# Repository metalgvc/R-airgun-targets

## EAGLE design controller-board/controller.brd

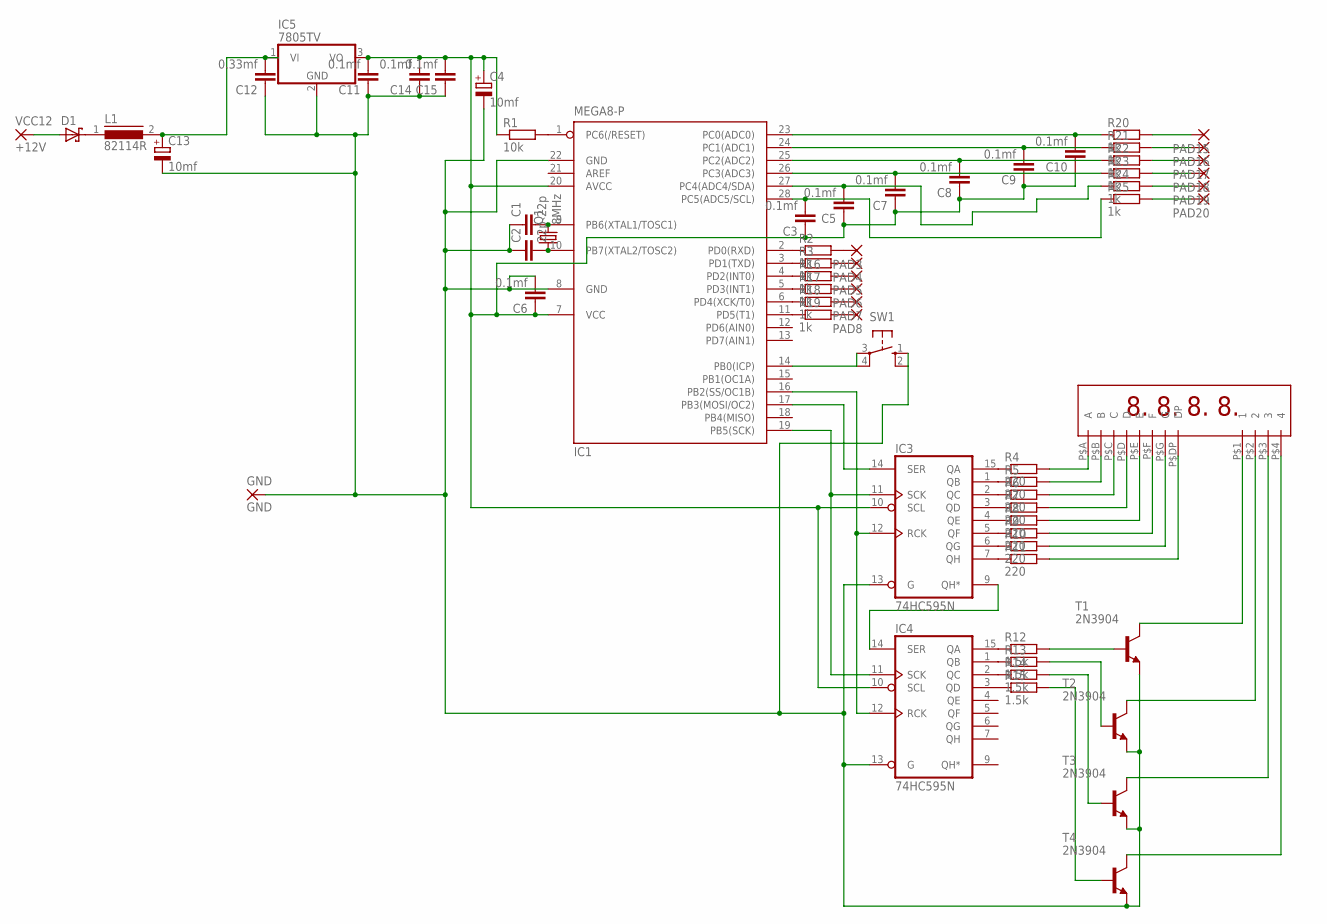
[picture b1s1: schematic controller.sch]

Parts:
C1, C2: 22p; C050-024X044
C3, C5, C6, C7, C8, C9, C10, C11, C14, C15: 0.1mf; C050-024X044
C4, C13: 10mf; E1,8-4
C12: 0.33mf; C050-024X044
D1: SCHOTTKY-DIODEDO35-7; DO35-7
GND: GND; 2,54/1,1
IC1: MEGA8-P; DIL28-3
IC3, IC4: 74HC595N; DIL16
IC5: 7805TV; TO220V
L1: 82114R
PAD3, PAD4, PAD5, PAD6, PAD7, PAD8, PAD15, PAD16, PAD17, PAD18, PAD19, PAD20: 1,6/0,8
Q1: 8MHz; HC49/S
R1: 10k; 0204/7
R2, R3, R16, R17, R18, R19, R20, R21, R22, R23, R24, R25: 1k; 0204/7
R4, R5, R6, R7, R8, R9, R10, R11: 220; 0204/7
R12, R13, R14, R15: 1.5k; 0204/7
SW1: 10-XX; B3F-10XX
T1, T2, T3, T4: 2N3904; TO92
U$1: KL-5641-ASR
VCC12: +12V; 2,54/1,1

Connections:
GND: C1.1, C2.1, C4.-, C6.2, C11.1, C12.1, C13.-, C14.1, C15.1, GND.1, IC1.8 (GND), IC1.22 (GND), IC3.8 (GND), IC3.13 (G), IC4.8 (GND), IC4.13 (G), IC5.2 (GND), SW1.1 (S), SW1.2 (S1), T1.3 (E), T2.3 (E), T3.3 (E), T4.3 (E)
unnamed: IC1.1 (PC6(/RESET)), R1.2
unnamed: D1.C, L1.1
unnamed: IC1.2 (PD0(RXD)), R2.1
unnamed: R4.2, U$1.P$A (A)
unnamed: R5.2, U$1.P$B (B)
unnamed: IC1.3 (PD1(TXD)), R3.1
unnamed: C1.2, IC1.9 (PB6(XTAL1/TOSC1)), Q1.2
unnamed: C2.2, IC1.10 (PB7(XTAL2/TOSC2)), Q1.1
unnamed: R6.2, U$1.P$C (C)
unnamed: R7.2, U$1.P$D (D)
unnamed: R8.2, U$1.P$E (E)
unnamed: R9.2, U$1.P$F (F)
unnamed: IC1.16 (PB2(SS/OC1B)), IC3.12 (RCK), IC4.12 (RCK)
unnamed: IC1.17 (PB3(MOSI/OC2)), IC3.14 (SER)
unnamed: IC1.19 (PB5(SCK)), IC3.11 (SCK), IC4.11 (SCK)
unnamed: C12.2, C13.+, IC5.1 (VI), L1.2
unnamed: R10.2, U$1.P$G (G)
unnamed: R11.2, U$1.P$DP (DP)
unnamed: IC3.15 (QA), R4.1
unnamed: IC3.1 (QB), R5.1
unnamed: IC3.2 (QC), R6.1
unnamed: IC3.3 (QD), R7.1
unnamed: IC3.4 (QE), R8.1
unnamed: IC3.5 (QF), R9.1
unnamed: IC3.6 (QG), R10.1
unnamed: IC3.7 (QH), R11.1
unnamed: IC4.15 (QA), R12.1
unnamed: IC4.1 (QB), R13.1
unnamed: IC4.2 (QC), R14.1
unnamed: IC4.3 (QD), R15.1
unnamed: R12.2, T1.2 (B)
unnamed: R13.2, T2.2 (B)
unnamed: R14.2, T3.2 (B)
unnamed: R15.2, T4.2 (B)
unnamed: D1.A, VCC12.1
unnamed: T1.1 (C), U$1.P$1 (1)
unnamed: T2.1 (C), U$1.P$2 (2)
unnamed: T3.1 (C), U$1.P$3 (3)
unnamed: T4.1 (C), U$1.P$4 (4)
unnamed: C10.2, IC1.23 (PC0(ADC0)), R20.1
unnamed: C9.2, IC1.24 (PC1(ADC1)), R21.1
unnamed: C8.2, IC1.25 (PC2(ADC2)), R22.1
unnamed: C7.2, IC1.26 (PC3(ADC3)), R23.1
unnamed: C5.2, IC1.27 (PC4(ADC4/SDA)), R24.1
unnamed: PAD16.1, R21.2
unnamed: IC1.4 (PD2(INT0)), R16.1
unnamed: IC1.5 (PD3(INT1)), R17.1
unnamed: IC1.6 (PD4(XCK/T0)), R18.1
unnamed: IC1.11 (PD5(T1)), R19.1
unnamed: PAD3.1, R2.2
unnamed: PAD4.1, R3.2
unnamed: PAD5.1, R16.2
unnamed: PAD6.1, R17.2
unnamed: PAD7.1, R18.2
unnamed: PAD8.1, R19.2
unnamed: IC1.14 (PB0(ICP)), SW1.3, SW1.4 (P1)
unnamed: PAD15.1, R20.2
unnamed: PAD17.1, R22.2
unnamed: PAD18.1, R23.2
unnamed: PAD19.1, R24.2
unnamed: PAD20.1, R25.2
unnamed: C3.2, IC1.28 (PC5(ADC5/SCL)), R25.1
unnamed: IC3.9 (QH*), IC4.14 (SER)
VCC: C3.1, C4.+, C5.1, C6.1, C7.1, C8.1, C9.1, C10.1, C11.2, C14.2, C15.2, IC1.7 (VCC), IC1.20 (AVCC), IC3.10 (SCL), IC3.16 (VCC), IC4.10 (SCL), IC4.16 (VCC), IC5.3 (VO), R1.1

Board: 2 copper layers, 67 parts (0 on the bottom side), 65 nets, no tracks yet.

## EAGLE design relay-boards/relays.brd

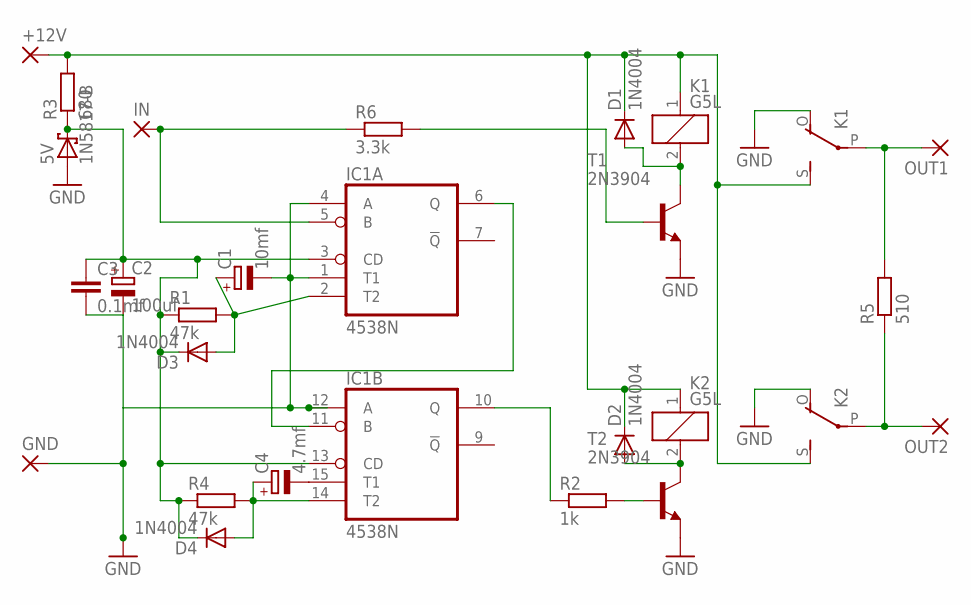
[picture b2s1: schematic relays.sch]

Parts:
5V: 1N5817-B; DO41-7.6
+12V: 3,81/1,1
C1: 10mf; E2,5-6E
C2: 100uf; E2,5-6E
C3: 0.1mf; C050-024X044
C4: 4.7mf; E2,5-6E
D1, D2, D3, D4: 1N4004; DO41-10
GND: 3,81/1,1
IC1: 4538N; DIL16
IN: 3,81/1,1
K1, K2: G5L; G5LE
OUT1, OUT2: 3,81/1,1
R1, R4: 47k; 0207/7
R2: 1k; 0207/7
R3: 680; 0207/7
R5: 510; 0207/7
R6: 3.3k; 0207/7
T1, T2: 2N3904; TO92

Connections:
GND: 5V.A, C1.-, C2.-, C3.2, GND.1, IC1.1 (T1), IC1.4 (A), IC1.12 (A), K1.O, K2.O, T1.3 (E), T2.3 (E)
unnamed: D1.A, K1.2, T1.1 (C)
unnamed: +12V.1, D1.C, D2.C, K1.1, K1.S, K2.1, K2.S, R3.2
unnamed: IC1.5 (B), IN.1, R6.1
unnamed: D2.A, K2.2, T2.1 (C)
unnamed: K1.P, OUT1.1, R5.2
unnamed: C1.+, D3.A, IC1.2 (T2), R1.2
unnamed: C4.-, IC1.15 (T1)
unnamed: IC1.6 (Q), IC1.11 (B)
unnamed: R2.2, T2.2 (B)
unnamed: K2.P, OUT2.1, R5.1
unnamed: IC1.10 (Q), R2.1
unnamed: C4.+, D4.A, IC1.14 (T2), R4.2
unnamed: R6.2, T1.2 (B)
VDD: 5V.C, C2.+, C3.1, D3.C, D4.C, IC1.3 (CD), IC1.13 (CD), IC1.16 (VDD), R1.1, R3.1, R4.1
VSS: IC1.8 (VSS)

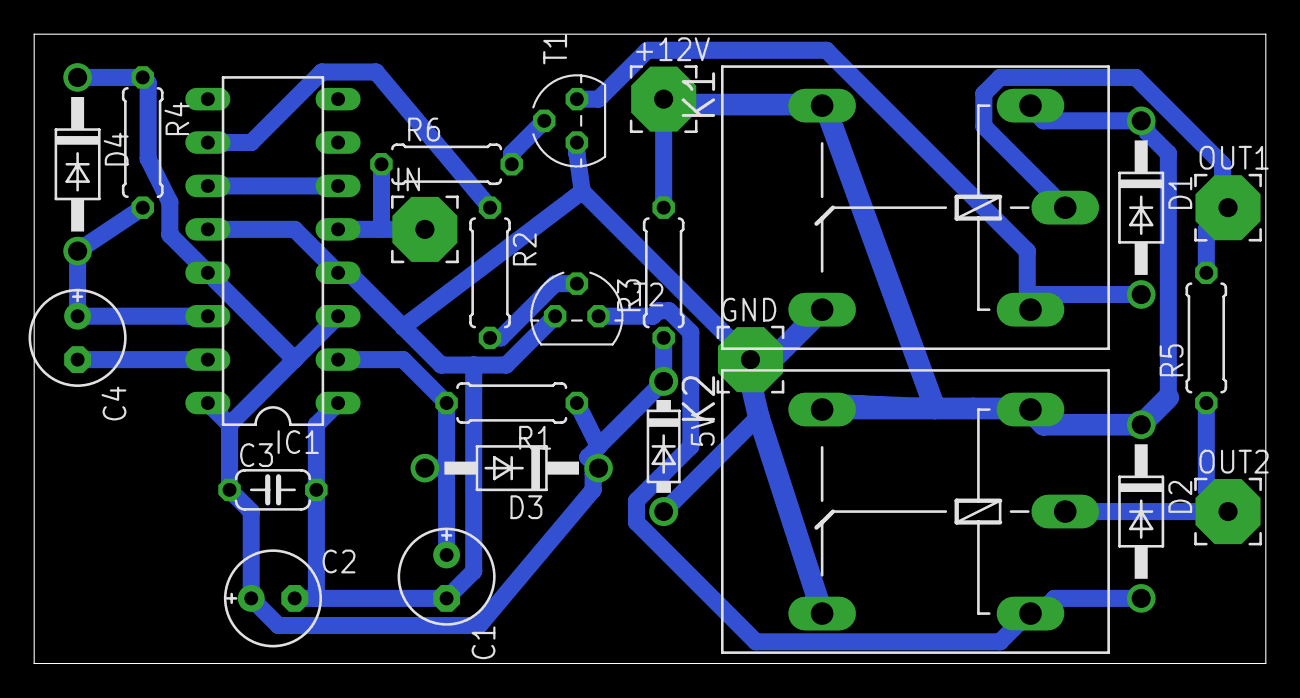
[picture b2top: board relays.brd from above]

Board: 2 copper layers, 72.1 x 36.8 mm, 25 parts (0 on the bottom side), 15 nets.

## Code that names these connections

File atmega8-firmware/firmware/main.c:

#include <avr/io.h>

#define F_CPU 8000000UL

int TIMER_MODE = 0;
int COUNTER_MODE = 1;

/*
 * set mode
 * 0 - TIMER - DONE
 * 1 - COUNTER -
 */
int MODE = 0;

int PAUSE = 1;
uint32_t PAUSE_LAST_TCOUNTER = 0;

#include <stdlib.h>
#include <stdint.h>
#include <util/delay.h>
#include <avr/interrupt.h>

#include "config.c"
#include "mylibs/timer.c"
#include "mylibs/SPI.c"
#include "mylibs/display.c"

#include "mylibs/core.c"
#include "TIMER_MODE.c"
#include "COUNTER_MODE.c"

void init(void);
void check_start_switch_mode_btn(void);

// debounce last time
uint32_t _swtchBtnLastTime = 0;
int _swtchBtnLastState = 0;

// ------- code --------

// init
void init(){
    sei(); // enable interrupts
    
    SPI_init();
    display_init();
    
    // set PORTC as input for target buttons
    //DDRC = 0b00000000; // 0 - input; 1 - output
    // set PC0-5 as input
    DDRC &= ~(1<<PC0) & ~(1<<PC1) & ~(1<<PC2) & ~(1<<PC3) & ~(1<<PC4) & ~(1<<PC5);
    PORTC |= (1<<PC0) | (1<<PC1) | (1<<PC2) | (1<<PC3) | (1<<PC4) | (1<<PC5); // PC0-5 high
    
    // set PORTD as output
    DDRD = 0b11111111;
    PORTD = 0b00000000; // set low on pins
    
    // set PINB0 for start/reset mode button as input
    DDRB &= ~(1<<PB0); // input
    PORTB |= (1<<PB0); // high
    
    init_timer();
    init_counter();
    
    // up targets
    //up_all_targets();
}


// main
int main(void)
{
    init();
    
    while (1) {
        
        check_start_switch_mode_btn();
        
        if (PAUSE == 1) {
            continue;
        }
        
        check_button(0, PC0); // btn1
        check_button(1, PC1); // btn2
        check_button(2, PC2); // btn3
        check_button(3, PC3); // btn4
        check_button(4, PC4); // btn5
        check_button(5, PC5); // btn6
        
// debug code ========================
//if (TCOUNTER > 1000) {
//    num1 = random_at_most(1);
//    num2 = random_at_most(2);
//    num3 = random_at_most(5);
//    num4 = random_at_most(9);
//    TCOUNTER = 0;
//}
//
//show_number();
//num1 = 1;
//num2 = 2;
//num3 = 3;
//num4 = 4;
//show_number();
//continue;
// end - debug code ==================
        
        // TIMER MODE
        if (MODE == TIMER_MODE) {
            
            main_timer();
            
        // COUNTER MODE
        } else if (MODE == COUNTER_MODE) {
            main_counter();
        }
        
    }
    
    return 0;
}

// reset/start/switch mode button
void check_start_switch_mode_btn(){
    
    // read reset/start btn
    if (GETBIT(PINB, PB0) == 0) { // pressed
        
        // dbounce counter
        if (_swtchBtnLastState == 0) {
            _swtchBtnLastState = 1;
            _swtchBtnLastTime = TCOUNTER;
        } else if (TCOUNTER > (_swtchBtnLastTime + 200 /*ms*/) ) {
            _swtchBtnLastTime = TCOUNTER; // switch mode each 200ms on btn pressed
            
            // handle PRESSED btn
            PAUSE = 1;
            PAUSE_LAST_TCOUNTER = TCOUNTER;
            int maxMode = 1;
            MODE++;
            if (MODE > maxMode) {
                MODE = 0;
            }
        }
    } else {
        // released btn
        _swtchBtnLastState = 0;
    }

    if (PAUSE == 1) {
        // show mode on display
        num1 = MODE; num2 = 0; num3 = 8; num4 = 8;
        show_number();
        
        // wait 3 second
        if ( (TCOUNTER - PAUSE_LAST_TCOUNTER)/TCOUNTER_DIVIDER > 3 ) {
            PAUSE = 0;
            num1 = 0; num2 = 0; num3 = 0; num4 = 0;
            
            if (MODE == TIMER_MODE) {
                init_timerm();
                TIMER_STARTED = 0;
            } else if (MODE == COUNTER_MODE) {
                init_counter();
                COUNTER = 0;
            }

        }
    }
}

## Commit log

2019-01-02 init
2019-01-12 forget xcode proj dir
